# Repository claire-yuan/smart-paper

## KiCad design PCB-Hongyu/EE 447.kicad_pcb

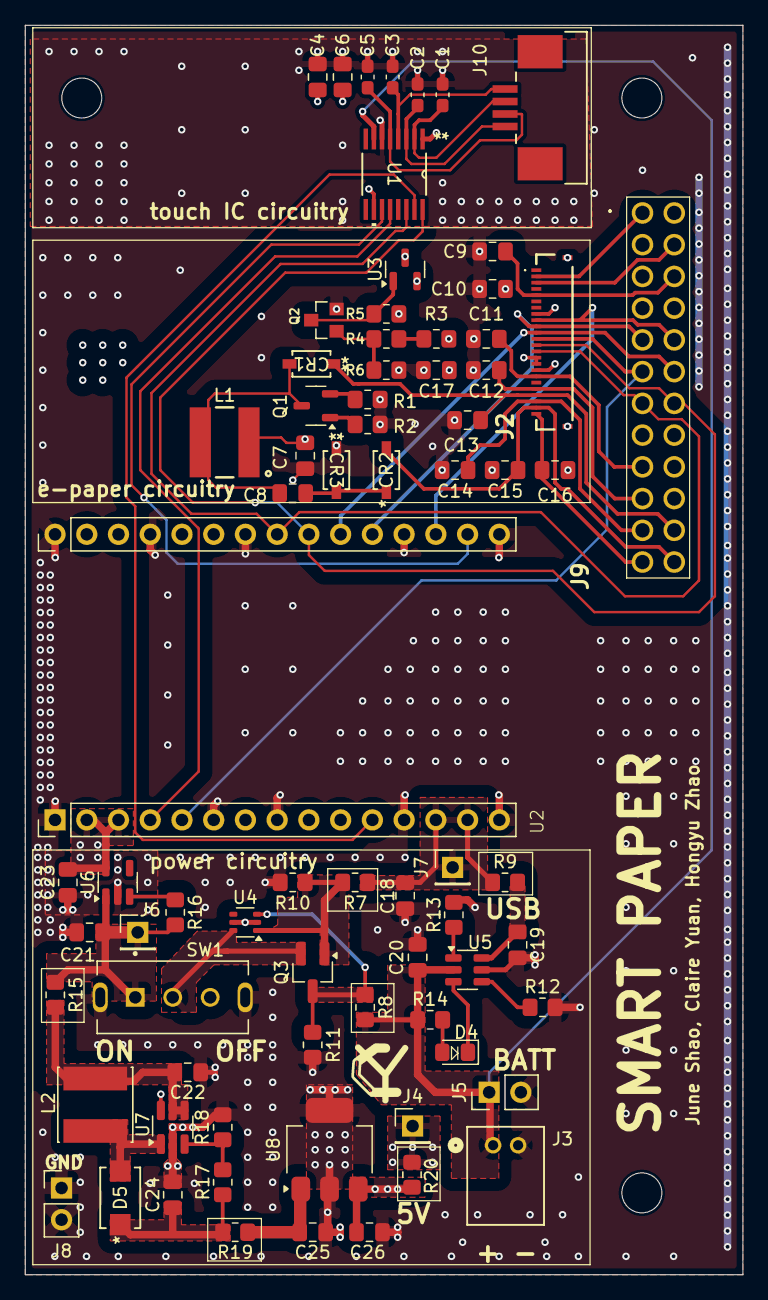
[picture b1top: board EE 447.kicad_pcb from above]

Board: 4 copper layers, 57.4 x 100.0 mm, 77 parts (0 on the bottom side), 49 nets.

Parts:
C1, C2, C3, C5: NC; C_0603_1608Metric_Pad1.08x0.95mm_HandSolder
C4, C20, C23, C24, C26: 10u; C_0805_2012Metric_Pad1.18x1.45mm_HandSolder
C6, C17: 0.1u; C_0805_2012Metric_Pad1.18x1.45mm_HandSolder
C7, C8, C21: 4.7u; C_0805_2012Metric_Pad1.18x1.45mm_HandSolder
C9, C10, C11, C12, C13, C14, C15, C16, C18, C19, C22, C25: 1u; C_0805_2012Metric_Pad1.18x1.45mm_HandSolder
CR1, CR2, CR3: SS0530_R1_00001; SOD-123_PNJ
D4: LTST-C171KRKT; LED_0805_2012Metric_Pad1.15x1.40mm_HandSolder
D5: B120AF-13; SDO_B120AF_DIO
H1, H2, H3: MountingHole; MountingHole_3.2mm_M3
J2: FH34SRJ-24S-0.5SH_99_; FH34SRJ24S05SH99
J3: S2B-PH-K-SLFSN; CONN_S2B-PH-K-S_JST
J4, J6, J7: Conn_01x01_Pin; PinHeader_1x01_P2.54mm_Vertical
J5, J8: Conn_01x02_Pin; PinHeader_1x02_P2.54mm_Vertical
J9: 61302421121
J10: 84952-4; CON4_SMT-RA_FCC-FPC2
L1: WE-MXGI_5030
L2: 3.3uH; IND_VLS6045AF-3R3N
Q1: BSS138; SOT-23-3
Q2: SMD-TRANSISTORS-NPN-25V-500MW_SOT-23_; S8050_SOT-23
Q3: DMG3415UQ-7; DMG3415UQ
R1: 0.47; R_0805_2012Metric_Pad1.20x1.40mm_HandSolder
R2, R4, R13: 10k; R_0805_2012Metric_Pad1.20x1.40mm_HandSolder
R3, R5: 47k; R_0805_2012Metric_Pad1.20x1.40mm_HandSolder
R6, R10, R11, R18: 100k; R_0805_2012Metric_Pad1.20x1.40mm_HandSolder
R7, R8, R9, R15, R19, R20: 0; R_0805_2012Metric_Pad1.20x1.40mm_HandSolder
R12: 5.36k; R_0805_2012Metric_Pad1.20x1.40mm_HandSolder
R14, R16: 1k; R_0805_2012Metric_Pad1.20x1.40mm_HandSolder
R17: 590k; R_0805_2012Metric_Pad1.20x1.40mm_HandSolder
SW1: SLW-121586-5A-D; SW_SLW-121586-5A-D
U1: TSC2046IPWR; PW16
U2: ESP32C3-mini-Devkit
U3: PJA3401A; SOT-23
U4: LM66100DCK; SOT-363_SC-70-6
U5: BQ21040DBV; SOT-23-6
U6: TLV75733PDBV; SOT-23-5
U7: TLV61048; SOT-23-6_Handsoldering
U8: MCP1825ST-3302E/DB; SOT-223-3_TabPin2

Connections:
+3.3V: C17.1, C23.1, R3.1, R5.1, U1.10 (IOVDD), U2.2 (3V3), U2.3 (3V3), U2.17 (TX), U2.18 (RX), U3.2, U6.5 (OUT)
+5V: C4.1, C6.1, J4.1, R20.2, U1.1 (VCC+)
+BATT: C20.1, J3.1, J5.1, R8.2, R14.1, U1.7 (VBAT), U5.2 (OUT)
/Epaper/3V3_OUT: C7.2, C10.1, J2.15, J2.16, J9.15, J9.16, L1.1, U3.3
/Epaper/EPD_PWR: R3.2, R4.2
/Epaper/GDR: J2.2, J9.1, Q1.1 (G), R2.2
/Epaper/RESE: J2.3, J9.4, Q1.2 (S), R1.1
/Epaper/SUB5: C9.1, J2.5, J9.6
/Epaper/SUB18: C11.1, J2.18, J9.17
/Epaper/SUB20: C12.1, J2.20, J9.19
/Epaper/SUB22: C14.1, J2.22, J9.21
/Epaper/SUB24: C16.1, J2.24, J9.23
/Epaper/VGH: C13.1, CR1.1, J2.21, J9.22
/Epaper/VGL: C15.1, CR2.2, J2.23, J9.24
/PENIRQ: U1.11 (*PENIRQ), U2.29 (IO19)
/Power/BATT_D: Q3.1 (D), R8.1, R11.1, U4.3 (~CE)
/Power/BOOST_FB: R17.2, R18.1, U7.3 (FB)
/Power/BOOST_SW: D5.2 (A), L2.2, U7.1 (SW)
/Power/BOOST_VIN: C22.1, L2.1, R15.2, U7.4 (EN), U7.5 (VIN)
/Power/BOOST_VOUT: C24.1, D5.1 (K), R17.1, R19.1
/Power/DIODE_OUT: Q3.3 (S), SW1.2 (B), U4.6 (VOUT)
/Power/LDO5V_VIN: C25.1, R19.2, U8.1 (VI)
/Power/LDO5V_VOUT: C26.1, R20.1, U8.3 (VO)
/Power/USB_IN: Q3.2 (G), R7.2, R10.1, U4.1 (VIN)
/Power/VIN_CHARGER: C19.1, R9.2, U5.6 (VIN)
CLK: J2.13, J9.14, U1.16 (DCLK), U2.24 (IO6)
CS_TSC: U1.15 (*CS), U2.11 (IO10)
EPD_BUSY: J2.9, J9.10, U2.28 (IO18)
EPD_CS: J2.12, J9.11, U2.5 (IO3)
EPD_DC: J2.11, J9.12, U2.25 (IO5)
EPD_RST: J2.10, J9.9, U2.26 (IO4)
GND: C1.2, C2.2, C3.2, C4.2, C5.2, C6.2, C7.1, C9.2, C10.2, C11.2, C12.2, C13.2, C14.2, C15.2, C16.2, C17.2, C18.2, C19.2, C20.2, C21.2, C22.2, C23.2, C24.2, C25.2, C26.2, CR3.1, J2.8, J2.17, J2.MP1, J2.MP2, J3.2, J5.2, J8.1, J8.2, J9.7, J9.18, Q2.2, R1.2, R2.1, R6.1, R10.2, R11.2, R12.2, R13.2, R18.2, SW1.SH1, SW1.SH2, U1.6 (GND), U2.1 (GND), U2.6 (GND), U2.8 (GND), U2.12 (GND), U2.15 (GND), U2.16 (GND), U2.19 (GND), U2.22 (GND), U2.27 (GND), U2.30 (GND), U4.2 (GND), U4.5 (ST), U5.5 (GND), U6.2 (GND), U7.2 (GND), U7.6 (FREQ), U8.2 (GND)
MISO: U1.12 (DOUT), U2.4 (IO2)
MOSI: J2.14, J9.13, U1.14 (DIN), U2.23 (IO7)
unnamed: C8.1, CR2.1, CR3.2
unnamed: D4.2 (A), R14.2
unnamed: D4.1 (K), U5.3 (~CHG)
unnamed: C8.2, CR1.2, L1.2, Q1.3 (D)
unnamed: Q2.1, R4.1, R6.2
unnamed: Q2.3, R5.2, U3.1
unnamed: C1.1, J10.3, U1.2 (X+)
unnamed: C3.1, J10.4, U1.4 (X-)
unnamed: C2.1, J10.1, U1.3 (Y+)
unnamed: C5.1, J10.2, U1.5 (Y-)
unnamed: R12.1, U5.4 (ISET)
unnamed: R13.1, U5.1 (TS)
unnamed: R16.2, U6.3 (EN)
VSOURCE: C21.1, J6.1, R15.1, R16.1, SW1.1 (A), U6.1 (IN)
VUSB: C18.1, J7.1, R7.1, R9.1, U2.13 (5V), U2.14 (5V)

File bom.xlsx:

Reference | Value | Footprint | Qty | Part Number | Datasheet
C1,C2,C3,C5 | NC | Capacitor_SMD:C_0603_1608Metric_Pad1.08x0.95mm_HandSolder | 4 |  | ~
C4,C20,C23,C24,C26 | 10u | Capacitor_SMD:C_0805_2012Metric_Pad1.18x1.45mm_HandSolder | 5 | GRM21BR61H106KE43L | https://www.digikey.com/en/products/detail/murata-electronic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
C6,C17 | 0.1u | Capacitor_SMD:C_0805_2012Metric_Pad1.18x1.45mm_HandSolder | 2 | CL21B104KBCNNNC | https://www.digikey.com/en/products/detail/samsung-electro-m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
C7,C8,C21 | 4.7u | Capacitor_SMD:C_0805_2012Metric_Pad1.18x1.45mm_HandSolder | 3 | GRM21BR61H475KE51L | https://www.digikey.com/en/products/detail/murata-electronic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
C9,C10,C11,C12,C13,C14,C15,C16,C18,C19,C22,C25 | 1u | Capacitor_SMD:C_0805_2012Metric_Pad1.18x1.45mm_HandSolder | 12 | CL21B105KBFNNNE | https://www.digikey.com/en/products/detail/samsung-electro-m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
CR1,CR2,CR3 | SS0530_R1_00001 | Library:SOD-123_PNJ | 3 |  | https://www.digikey.com/en/products/detail/panjit-internatio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
D4 | LTST-C171KRKT | LED_SMD:LED_0805_2012Metric_Pad1.15x1.40mm_HandSolder | 1 |  | https://www.digikey.com/en/products/detail/liteon/LTST-C171K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
D5 | B120AF-13 | Library:SDO_B120AF_DIO | 1 |  | https://www.digikey.com/en/products/detail/diodes-incorporat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
J2 | FH34SRJ-24S-0.5SH_99_ | Custom:FH34SRJ24S05SH99 | 1 |  | https://www.mouser.com/ProductDetail/Hirose-Connector/FH34SR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
J3 | S2B-PH-K-SLFSN | Library:CONN_S2B-PH-K-S_JST | 1 |  | https://www.digikey.com/en/products/detail/jst-sales-america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
J4,J6,J7 | Conn_01x01_Pin | Connector_PinHeader_2.54mm:PinHeader_1x01_P2.54mm_Vertical | 3 |  | ~
J5,J8 | Conn_01x02_Pin | Connector_PinHeader_2.54mm:PinHeader_1x02_P2.54mm_Vertical | 2 |  | ~
J9 | 61302421121 | Custom:61302421121 | 1 |  | https://www.mouser.com/ProductDetail/Wurth-Elektronik/613024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
J10 | 84952-4 | Hongyu:CON4_SMT-RA_FCC-FPC2 | 1 | 84952-4 | https://www.digikey.com/en/products/detail/te-connectivity-a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
L1 | WE-MXGI_5030 | Custom:WE-MXGI_5030 | 1 |  | https://www.digikey.com/en/products/detail/w%C3%BCrth-elektr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
L2 | 3.3uH | Library:IND_VLS6045AF-3R3N | 1 |  | https://www.digikey.com/en/products/detail/tdk-corporation/V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
Q1 | BSS138 | Package_TO_SOT_SMD:SOT-23-3 | 1 |  | https://www.mouser.com/ProductDetail/onsemi-Fairchild/BSS138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
Q2 | SMD-TRANSISTORS-NPN-25V-500MW_SOT-23_ | Library:S8050_SOT-23 | 1 |  | https://www.digikey.com/en/products/detail/umw/S8050/17635323
Q3 | DMG3415UQ-7 | Library:DMG3415UQ | 1 |  | https://www.digikey.com/en/products/detail/diodes-incorporat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
R1 | 0.47 | Resistor_SMD:R_0805_2012Metric_Pad1.20x1.40mm_HandSolder | 1 |  | https://www.digikey.com/en/products/detail/littelfuse-inc/WS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
R2,R4,R13 | 10k | Resistor_SMD:R_0805_2012Metric_Pad1.20x1.40mm_HandSolder | 3 | RC0805FR-0710KL | https://www.digikey.com/en/products/detail/yageo/RC0805FR-07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
R3,R5 | 47k | Resistor_SMD:R_0805_2012Metric_Pad1.20x1.40mm_HandSolder | 2 |  | https://www.digikey.com/en/products/detail/stackpole-electro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
R6,R10,R11,R18 | 100k | Resistor_SMD:R_0805_2012Metric_Pad1.20x1.40mm_HandSolder | 4 | AC0805FR-07100KL | https://www.digikey.com/en/products/detail/yageo/ac0805fr-07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
R7,R8,R9,R15,R19,R20 | 0 | Resistor_SMD:R_0805_2012Metric_Pad1.20x1.40mm_HandSolder | 6 | RC0805JR-070RL | https://www.digikey.com/en/products/detail/yageo/RC0805JR-07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
R12 | 5.36k | Resistor_SMD:R_0805_2012Metric_Pad1.20x1.40mm_HandSolder | 1 | ERA-6AEB5361V | https://www.digikey.com/en/products/detail/panasonic-electro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
R14,R16 | 1k | Resistor_SMD:R_0805_2012Metric_Pad1.20x1.40mm_HandSolder | 2 | AC0805FR-071KL | https://www.digikey.com/en/products/detail/yageo/AC0805FR-07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
R17 | 590k | Resistor_SMD:R_0805_2012Metric_Pad1.20x1.40mm_HandSolder | 1 | RC0805FR-07590KL | https://www.digikey.com/en/products/detail/yageo/RC0805FR-07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
SW1 | SLW-121586-5A-D | Library:SW_SLW-121586-5A-D | 1 |  | https://www.digikey.com/en/products/detail/same-sky-formerly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
U1 | TSC2046IPWR | PW16 | 1 | TSC2046IPWR | https://www.digikey.com/en/products/detail/texas-instruments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
U2 | ~ | Library:ESP32C3-mini-Devkit | 1
U3 | PJA3401A | Package_TO_SOT_SMD:SOT-23 | 1 |  | https://www.mouser.com/ProductDetail/Panjit/PJA3401A_R1_0000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
U4 | LM66100DCK | Package_TO_SOT_SMD:SOT-363_SC-70-6 | 1 |  | https://www.digikey.com/en/products/detail/texas-instruments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
U5 | BQ21040DBV | Package_TO_SOT_SMD:SOT-23-6 | 1 |  | https://www.digikey.com/en/products/detail/texas-instruments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
U6 | TLV75733PDBV | Package_TO_SOT_SMD:SOT-23-5 | 1 |  | https://www.digikey.com/en/products/detail/texas-instruments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
U7 | TLV61048 | Package_TO_SOT_SMD:SOT-23-6_Handsoldering | 1 |  | https://www.digikey.com/en/products/detail/texas-instruments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
U8 | MCP1825ST-3302E/DB | Package_TO_SOT_SMD:SOT-223-3_TabPin2 | 1 |  | https://www.digikey.com/en/products/detail/microchip-technol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

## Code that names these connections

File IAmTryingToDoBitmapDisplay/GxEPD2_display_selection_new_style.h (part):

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
// SS is usually used for CS. define here for easy change
#ifndef EPD_CS
#define EPD_CS SS
#endif

#if defined(GxEPD2_DISPLAY_CLASS) && defined(GxEPD2_DRIVER_CLASS)
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#if defined (ARDUINO_AVR_MEGA2560) // Note: SS is on 53 on MEGA
#define MAX_DISPLAY_BUFFER_SIZE 5000 // e.g. full height for 200x200
#elif defined(ARDUINO_AVR_NANO_EVERY)
#define EPD_CS 10
#define MAX_DISPLAY_BUFFER_SIZE 5000 // e.g. full height for 200x200
#else // Note: SS is on 10 on UNO, NANO
#define MAX_DISPLAY_BUFFER_SIZE 800 // 
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// needs jumpers from PA5 (PIN_SPI_SCK) to SCK for EPD and PA7 (PIN_SPI_MOSI) to SDI for EPD. PD9 and PD10 are not HW SPI capable.
//GxEPD2_DISPLAY_CLASS<GxEPD2_DRIVER_CLASS, MAX_HEIGHT(GxEPD2_DRIVER_CLASS)> display(GxEPD2_DRIVER_CLASS(/*CS=*/ PD8, /*DC=*/ PE15, /*RST=*/ PE14, /*BUSY=*/ PE13));
//GxEPD2_DISPLAY_CLASS<GxEPD2_DRIVER_CLASS, MAX_HEIGHT(GxEPD2_DRIVER_CLASS)> display(GxEPD2_DRIVER_CLASS(/*CS=*/ PD8, /*DC=*/ PE15, /*RST=*/ PE14, /*BUSY=*/ PE13, /*CS2=*/ PD12)); // for GDEM1085T51
GxEPD2_DISPLAY_CLASS<GxEPD2_DRIVER_CLASS, MAX_HEIGHT(GxEPD2_DRIVER_CLASS)> display(GxEPD2_DRIVER_CLASS(/*CS=PA4*/ EPD_CS, /*DC=*/ PA3, /*RST=*/ PA2, /*BUSY=*/ PA1)); // my proto board
#undef MAX_DISPLAY_BUFFER_SIZE
#undef MAX_HEIGHT
#endif
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#endif
#if defined(ARDUINO_ADAFRUIT_FEATHER_RP2040_THINKINK)
// Adafruit Feather RP2040 ThinkInk used with package https://github.com/earlephilhower/arduino-pico
GxEPD2_DISPLAY_CLASS<GxEPD2_DRIVER_CLASS, MAX_HEIGHT(GxEPD2_DRIVER_CLASS)> display(GxEPD2_DRIVER_CLASS(/*CS=*/ PIN_EPD_CS, /*DC=*/ PIN_EPD_DC, /*RST=*/ PIN_EPD_RESET, /*BUSY=*/ PIN_EPD_BUSY));
#endif
#undef MAX_DISPLAY_BUFFER_SIZE
#undef MAX_HEIGHT
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
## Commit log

2025-03-02 tsc2046 SPI code in progress
2025-03-11 touch IC code works. diagonal finger test
2025-03-24 touch IC reads correct position now
2025-03-25 get waveshare spi working
2025-03-30 schematic done
2025-03-31 MCU + Touch IC
2025-03-31 power circuits for pcb
2025-03-31 lllllllllllllllllllllllllllllllllll
2025-03-31 changed numbers to avoid conflict, added shared libraries
2025-03-31 added all schematics together
2025-03-31 testing
2025-03-31 1345678
2025-03-31 started layout placement
2025-04-02 updated power circuitry
2025-04-03 spi global pins
2025-04-03 power nets
2025-04-04 routed power circuitry
2025-04-04 copper pours
2025-04-06 power - added headers, decoupling cap, changed inductor, 3d models
2025-04-09 touch ic mostly routed
2025-04-10 i changed the FPC on my schematic
2025-04-10 i hope this is right
2025-04-10 I HOPE THIS WORKS
2025-04-10 hhhhh
2025-04-10 file
2025-04-10 annotate
2025-04-10 footprints
2025-04-10 added pinheader
2025-04-10 adapter
2025-04-10 i added stuff
2025-04-10 asdfasdfasf
2025-04-10 changed inductor. did some SPICE sims
2025-04-11 routed spi
2025-04-12 almost done
2025-04-13 claire can i get inductor footprint haha
2025-04-13 footprint
2025-04-15 added power digikey links
2025-04-15 added some stuff
2025-04-15 finished adding parts and fixing silkscreen
2025-04-16 i try edit stuff but NOT LET ME SYMbOL so i say claire do it hehe ty
2025-04-16 footprint pull push
2025-04-16 eieio i think i done
2025-04-16 small fixes
2025-04-16 grounding fpc mounting
2025-04-17 sdfghjk
2025-04-17 i think i changed it good maybe
2025-04-17 silkscreen
2025-04-17 checked DRC but check again ig, i checked all my footprint
    i made a small change connecting 15 and 16
2025-04-17 penirq change pin
2025-04-17 gerbers
2025-04-20 created my folder
2025-04-20 integrated both touch and display together
2025-04-20 BLE code for ESP32 and python script for laptop
2025-04-21 updated code to write to display from touch array
2025-04-22 finished code to send bytes over BLE and store in IMAGE_DATA
2025-04-25 wertyuio
2025-04-27 partial refresh working + CAD
2025-04-28 schematic glitch, layout has unconnected nets
2025-04-28 udpated code
2025-04-28 code integration started
2025-04-28 mememmemememe
2025-04-28 calibration code not working :(
2025-04-28 i think im done, combined the ble and my code.
2025-04-28 added some more 3d models
2025-04-29 models added
2025-04-29 meep
2025-04-29 updated files
2025-04-29 fixed int divison
2025-04-29 it Works! (kina)
2025-04-29 changes?
2025-04-29 updated final code
2025-04-29 pushing all updates
2025-04-30 added back annotations
